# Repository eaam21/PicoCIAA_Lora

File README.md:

Poncho Lora (RFM95W) para la PicoCIAA

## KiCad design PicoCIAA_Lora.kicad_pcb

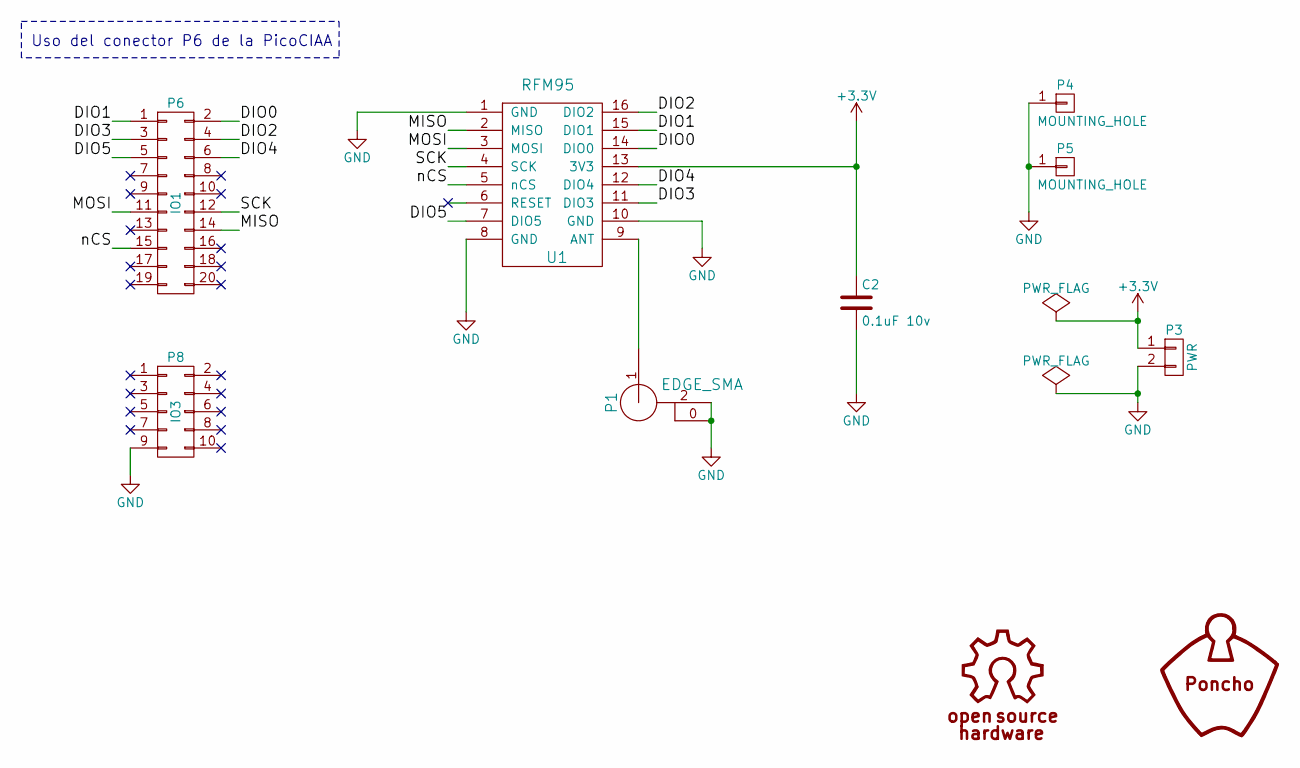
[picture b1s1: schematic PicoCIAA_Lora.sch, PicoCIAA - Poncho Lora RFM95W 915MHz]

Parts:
C2: 0.1uF 10v; C_0805; Digikey# 399-3520-1-ND
P1: EDGE_SMA; SMA_EDGE
P3: PWR; Pin_Header_Straight_1x02_Pitch2.00mm; Digikey# SAM1247-02-ND
P4, P5: MOUNTING_HOLE; PIN_ARRAY_1
P6: IO1; Pin_Header_Straight_2x10_Pitch2.00mm; Digikey# 952-1361-5-ND
P8: IO3; Pin_Header_Straight_2x05_Pitch2.00mm; Digikey# 952-1359-5-ND
U1: RFM95; RFM95W; Digikey# RFM95W-915S2-ND

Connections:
+3V3: C2.1, P3.1, U1.13 (3V3)
/DIO0: P6.2, U1.14 (DIO0)
/DIO1: P6.1, U1.15 (DIO1)
/DIO2: P6.4, U1.16 (DIO2)
/DIO3: P6.3, U1.11 (DIO3)
/DIO4: P6.6, U1.12 (DIO4)
/DIO5: P6.5, U1.7 (DIO5)
/MISO: P6.14, U1.2 (MISO)
/MOSI: P6.11, U1.3 (MOSI)
/SCK: P6.12, U1.4 (SCK)
/nCS: P6.15, U1.5 (nCS)
GND: C2.2, P1.0, P1.2 (GND), P3.2, P4.1, P5.1, P8.9, U1.1 (GND), U1.8 (GND), U1.10 (GND)
unnamed: P1.1 (RF), U1.9 (ANT)

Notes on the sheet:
Uso del conector P6 de la PicoCIAA

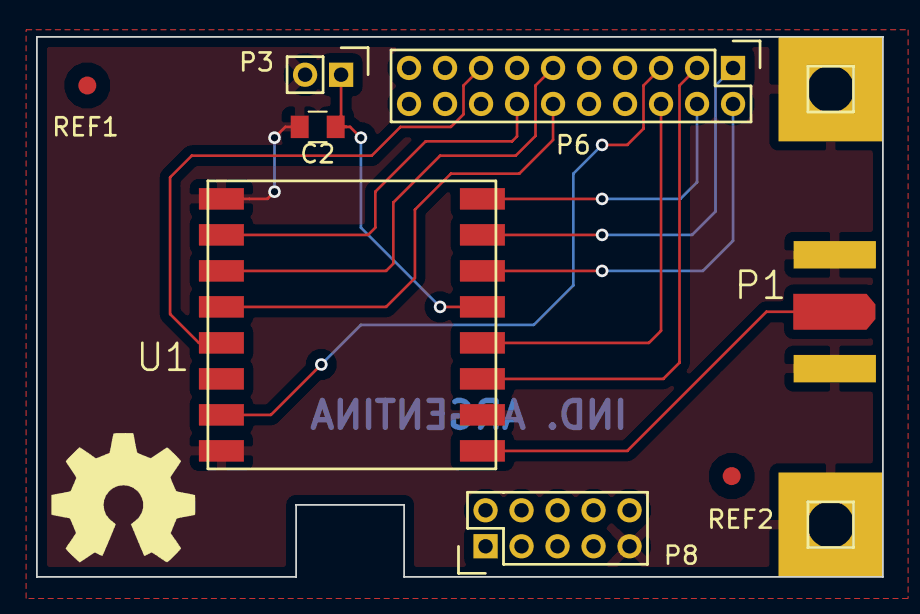
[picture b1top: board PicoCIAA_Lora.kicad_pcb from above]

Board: 2 copper layers, 47.0 x 30.0 mm, 11 parts (0 on the bottom side), 13 nets.

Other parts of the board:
G101: Logo_OSHWA
REF1: F1; Fiducial_1mm_Dia_2.54mm_Outer_CopperTop
REF2: F2; Fiducial_1mm_Dia_2.54mm_Outer_CopperTop

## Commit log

2017-05-22 Primer commit
2017-05-26 Agregando Hoja de datos RFM95_96_97_98W
2017-05-28 Agregando footprint RFM95W
2017-05-28 Primer avance del esquema
2017-06-10 Agregando Hoja de datos PicoCIAA
2017-06-11 Actualizando esquemático
2017-06-11 lib: actualizando libreria de esquemático
2017-06-11 doc/LICENCIA.txt: Agregando licencia
2017-06-11 footprints: agregando Conector y conector SMA
2017-06-17 footprints: agregando Conector de mounting hole
2017-06-17 footprints: modificando footprints
2017-06-17 Actualizando esquema
2017-06-17 lib/PicoLora.lib: modificando lista de simbolos
2017-06-24 PCB: Delimitando con bordes
2017-06-24 PCB: Delimitando boton reset
2017-07-07 doc: organizando doc
2017-07-07 SCH: Actualizando esquematico
2017-07-07 SCH: Actualizando uso de biblioteca
2017-07-10 SCH: Agregando campo DigiKey
2017-07-15 PCB: ruteando
2017-07-16 SCH: Actualizando esquema
2017-07-16 PCB: completando ruteo
2017-07-16 PCB: agregando componentes 3D
2017-07-16 PCB: agregando zonas de cobre
2017-07-26 DOC: Revision 2
2017-07-26 PCB: Cambiando footprint capacitor a 0805
2017-07-26 Agregando .gitignore
2017-07-26 PCB: Borde para reset
2017-08-10 DOC: agregando estandares Mayer
2017-08-12 PCB: modificando via y pista
2017-08-12 SCH: Agregando revisor
2017-08-12 PCB: Agregando notas de fabricación
2017-08-12 PCB: Agregado Rotulo
2017-08-12 PCB: Agregando fiduciales
2017-08-12 DOC: agregando revision
2017-08-12 PCB: Acomodando 3D
2017-08-12 Agregando Logos footprint
2017-08-12 DRC: Prueba
